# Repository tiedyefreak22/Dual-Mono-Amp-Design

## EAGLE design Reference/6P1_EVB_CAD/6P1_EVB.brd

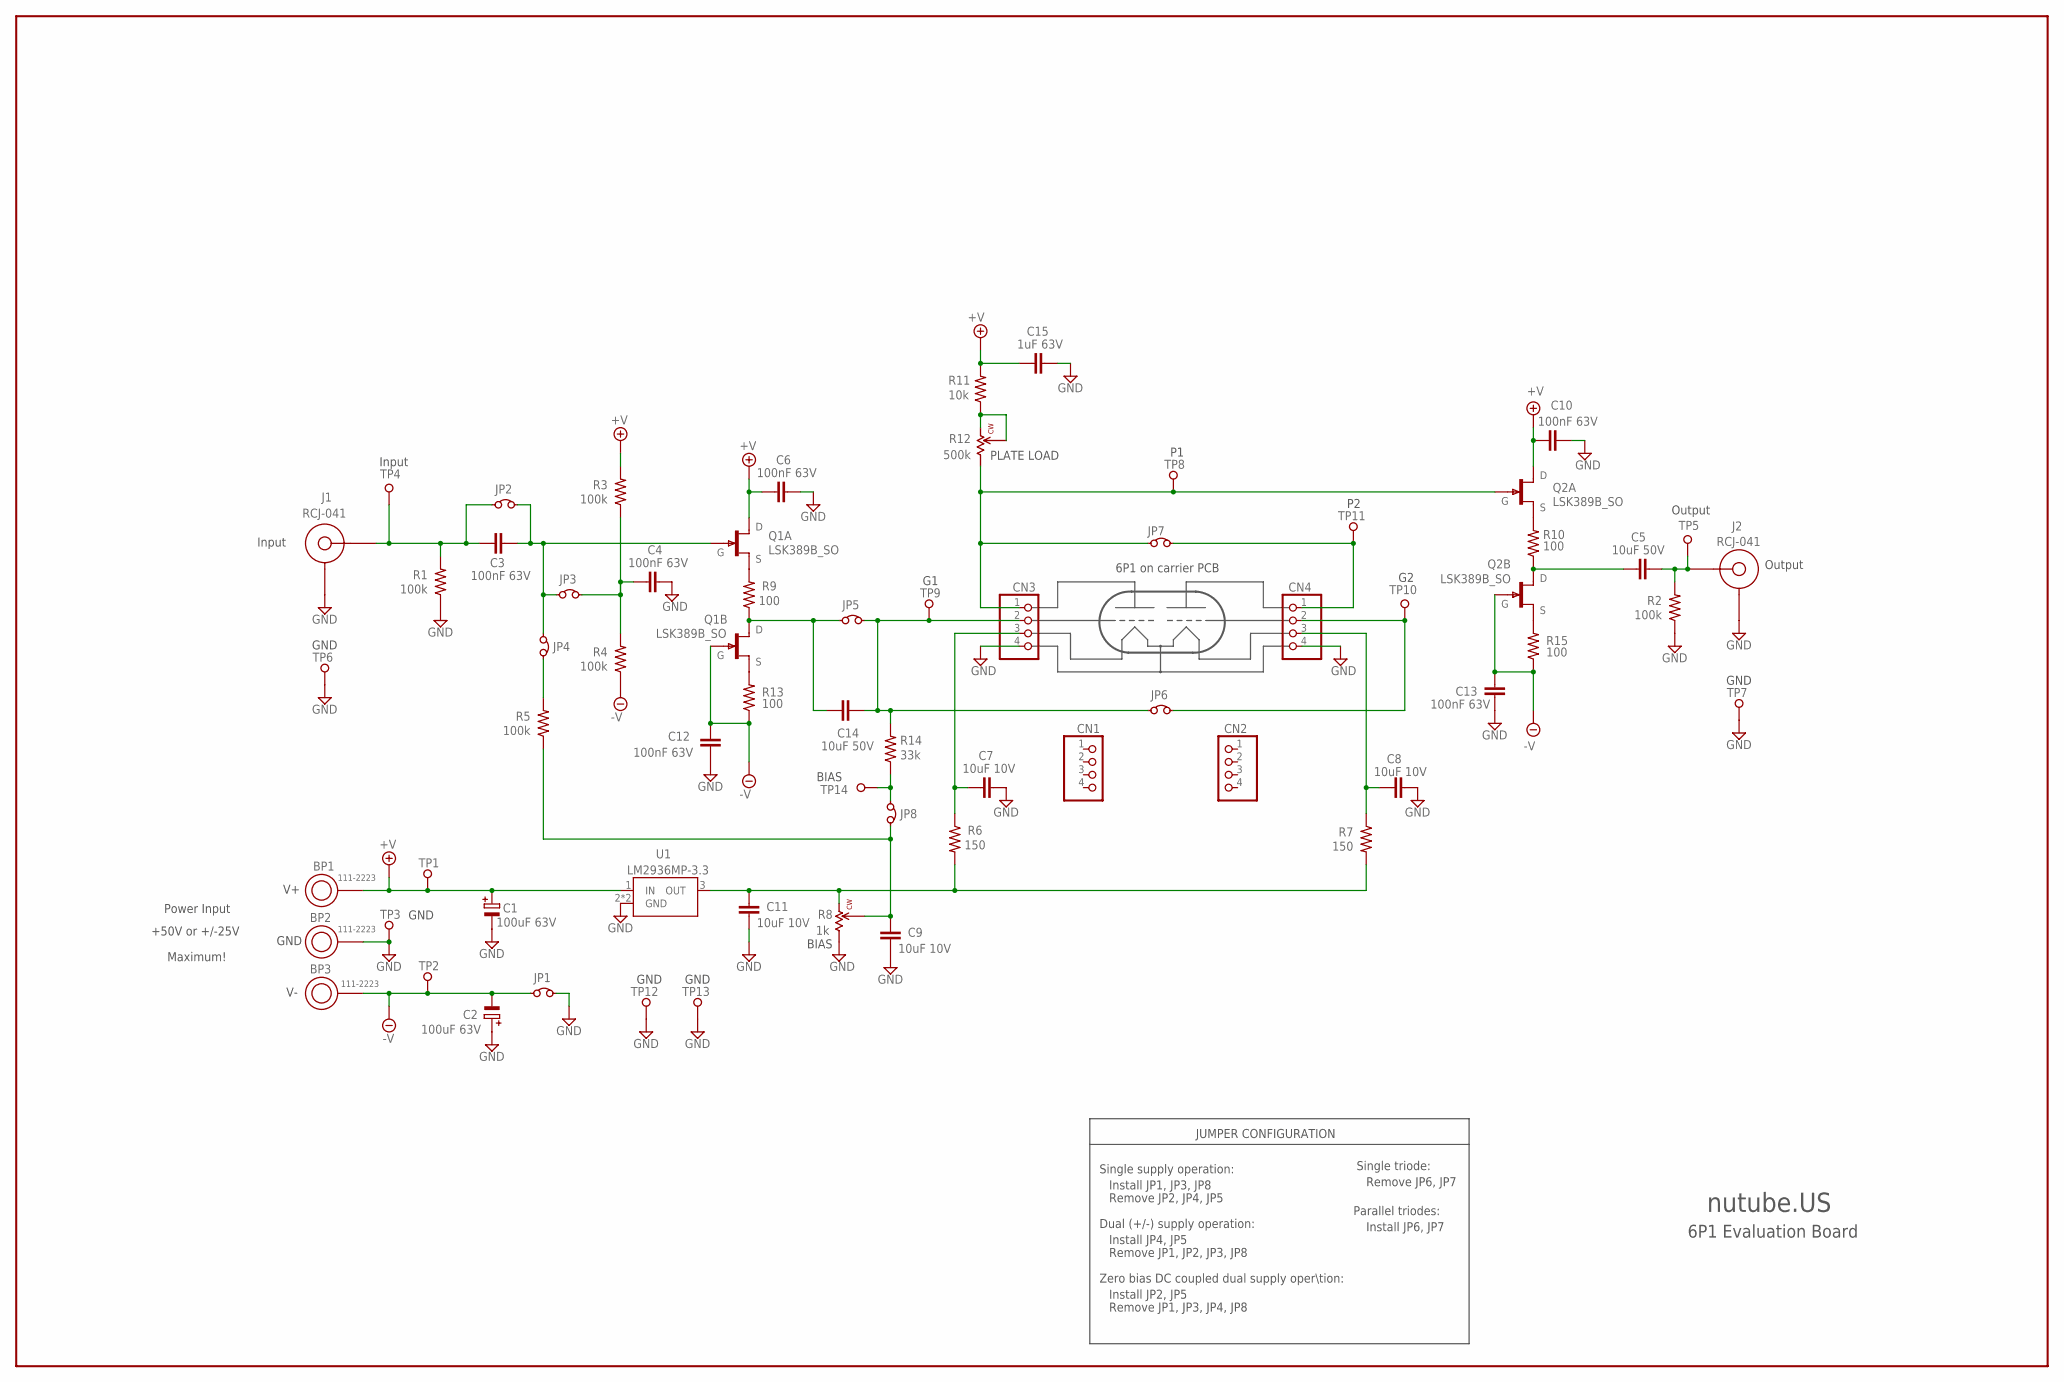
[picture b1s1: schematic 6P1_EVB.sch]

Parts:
BP1, BP2, BP3: 111-2223; BANANA_BP
C1, C2: 100uF 63V; ELCAP_SMT_10MM
C3, C4, C6, C10, C12, C13: 100nF 63V; C050-030X075
C5, C14: 10uF 50V; C050-110X075
C7, C8, C9, C11: 10uF 10V; C1206
C15: 1uF 63V; C050-050X075
CN1, CN2, CN3, CN4: PINHD-1X4; 1X04
J1, J2: RCJ-041; JACK_RCA
JP1, JP2, JP3, JP4, JP5, JP6, JP7, JP8: JUMPER; HDR2X1
Q1, Q2: LSK389B_SO; SO8
R1, R2, R3, R4, R5: 100k; R0805
R6, R7: 150; R0805
R8: 1k; TRIMPOT_3266
R9, R10, R13, R15: 100; R0805
R11: 10k; R0805
R12: 500k; TRIMPOT_3266
R14: 33k; R0805
TP1, TP2, TP3, TP4, TP5, TP6, TP7, TP8, TP9, TP10, TP11, TP12, TP13, TP14: TESTPOINT; TESTPOINT_63
U1: LM2936MP-3.3; SOT223-3

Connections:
+V: BP1.P$2, C1.P$1 (+), C6.2, C10.2, C15.2, Q1.2 (D), Q2.2 (D), R3.2, R11.2, TP1.P$1, U1.1 (IN)
-V: BP3.P$2, C2.P$2 (-), C12.2, C13.2, JP1.1, Q1.8 (G), Q2.8 (G), R4.1, R13.1, R15.1, TP2.P$1
G1: C14.1, CN3.2, JP5.2, JP6.1, R14.2, TP9.P$1
G2: CN4.2, JP6.2, TP10.P$1
GND: BP2.P$2, C1.P$2 (-), C2.P$1 (+), C4.1, C6.1, C7.2, C8.2, C9.2, C10.1, C11.2, C12.1, C13.1, C15.1, CN3.4, CN4.4, J1.P$1 (3), J2.P$1 (3), JP1.2, R1.1, R2.1, R8.1, TP3.P$1, TP6.P$1, TP7.P$1, TP12.P$1, TP13.P$1, U1.2 (GND), U1.4 (GND)
INL: C3.1, JP2.2, JP3.1, JP4.1, Q1.4 (G)
unnamed: Q1.1 (S), R9.2
unnamed: C14.2, JP5.1, Q1.6 (D), R9.1
unnamed: R11.1, R12.2, R12.3
unnamed: C7.1, CN3.3, R6.1
unnamed: C3.2, J1.P$2 (1), JP2.1, R1.2, TP4.P$1
unnamed: JP4.2, R5.2
unnamed: Q2.5 (S), R15.2
unnamed: Q2.1 (S), R10.2
unnamed: C5.2, Q2.6 (D), R10.1
unnamed: C5.1, J2.P$2 (1), R2.2, TP5.P$1
unnamed: Q1.5 (S), R13.2
unnamed: C8.1, CN4.3, R7.1
unnamed: C4.2, JP3.2, R3.1, R4.2
unnamed: C9.1, JP8.2, R5.1, R8.2
unnamed: JP8.1, R14.1, TP14.P$1
unnamed: CN3.1, JP7.1, Q2.4 (G), R12.1, TP8.P$1
PLATEL: CN4.1, JP7.2, TP11.P$1
V33: C11.1, R6.2, R7.2, R8.3, U1.3 (OUT)

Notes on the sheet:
6P1 Evaluation Board
nutube.US
GND
Maximum!
Power Input
+50V or +/-25V
Input
Output
BIAS
6P1 on carrier PCB
Single supply operation:
Install JP1, JP3, JP8
Remove JP2, JP4, JP5
Dual (+/-) supply operation:
Install JP4, JP5
Remove JP1, JP2, JP3, JP8
Zero bias DC coupled dual supply oper\tion:
Install JP2, JP5
Remove JP1, JP3, JP4, JP8
JUMPER CONFIGURATION
Single triode:
Remove JP6, JP7
Parallel triodes:
Install JP6, JP7
PLATE LOAD

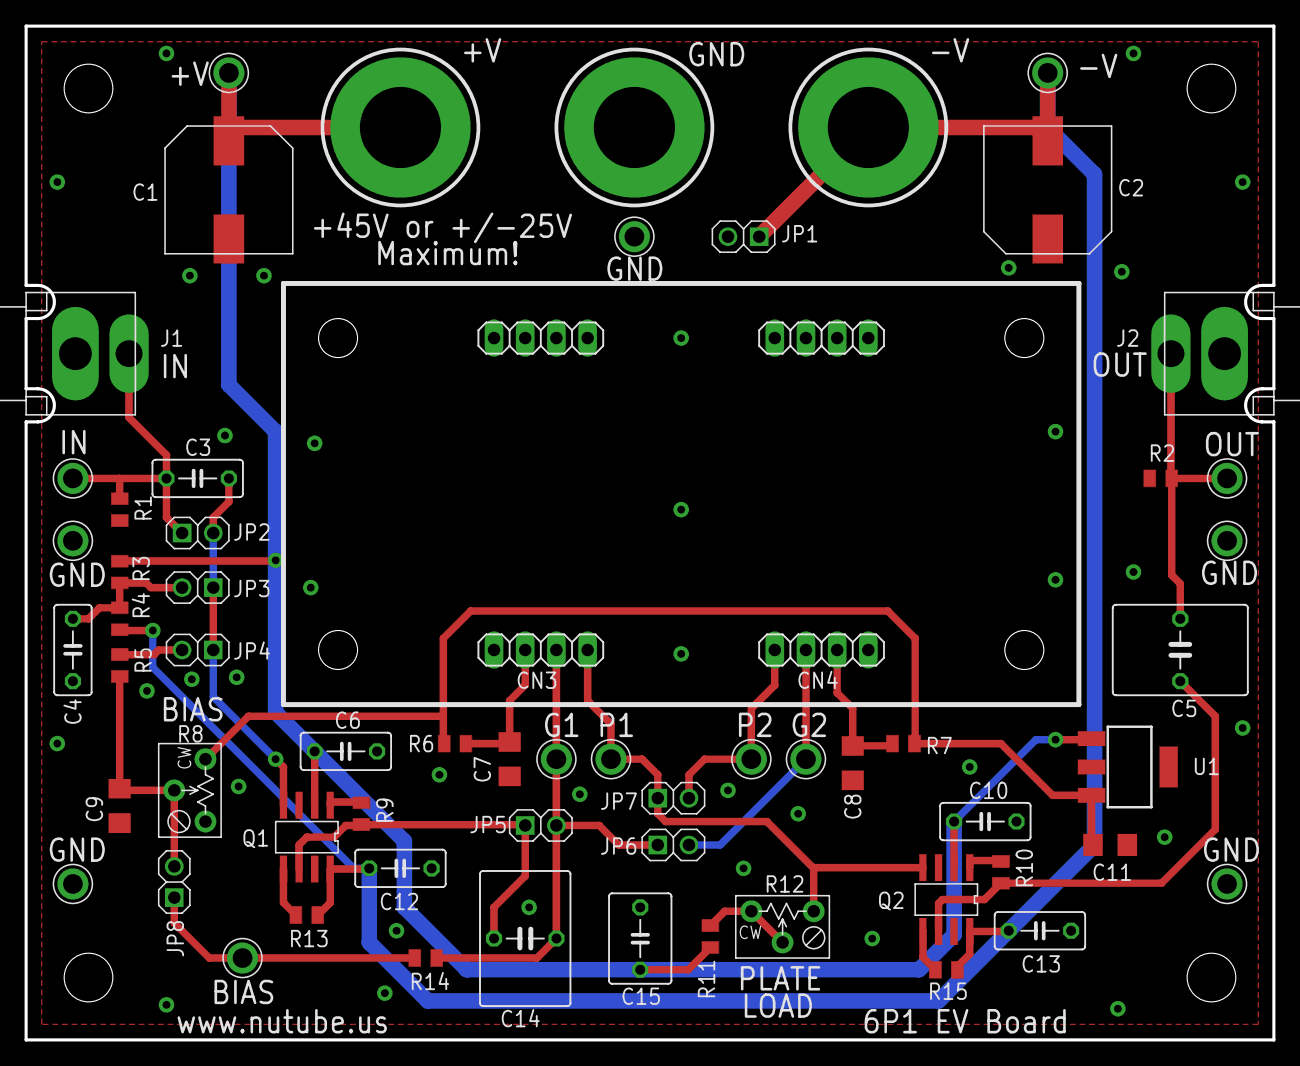
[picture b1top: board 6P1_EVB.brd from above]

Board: 2 copper layers, 101.6 x 82.5 mm, 64 parts (0 on the bottom side), 24 nets.

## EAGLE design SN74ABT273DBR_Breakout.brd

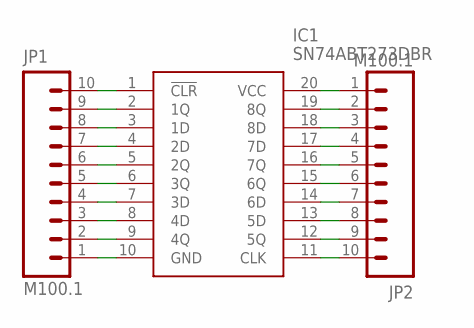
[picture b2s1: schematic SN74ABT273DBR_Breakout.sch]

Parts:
IC1: SN74ABT273DBR; SOP65P780X200-20N
JP1, JP2: M100.1; 1X10

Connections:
unnamed: IC1.10 (GND), JP1.1
unnamed: IC1.9 (4Q), JP1.2
unnamed: IC1.8 (4D), JP1.3
unnamed: IC1.7 (3D), JP1.4
unnamed: IC1.6 (3Q), JP1.5
unnamed: IC1.5 (2Q), JP1.6
unnamed: IC1.4 (2D), JP1.7
unnamed: IC1.3 (1D), JP1.8
unnamed: IC1.2 (1Q), JP1.9
unnamed: IC1.1 (!CLR), JP1.10
unnamed: IC1.20 (VCC), JP2.1
unnamed: IC1.19 (8Q), JP2.2
unnamed: IC1.18 (8D), JP2.3
unnamed: IC1.17 (7D), JP2.4
unnamed: IC1.16 (7Q), JP2.5
unnamed: IC1.15 (6Q), JP2.6
unnamed: IC1.14 (6D), JP2.7
unnamed: IC1.13 (5D), JP2.8
unnamed: IC1.12 (5Q), JP2.9
unnamed: IC1.11 (CLK), JP2.10

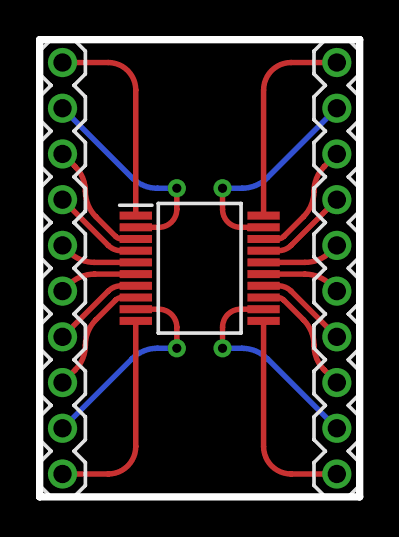
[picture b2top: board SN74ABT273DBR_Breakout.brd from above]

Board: 2 copper layers, 17.8 x 25.4 mm, 3 parts (0 on the bottom side), 20 nets.
